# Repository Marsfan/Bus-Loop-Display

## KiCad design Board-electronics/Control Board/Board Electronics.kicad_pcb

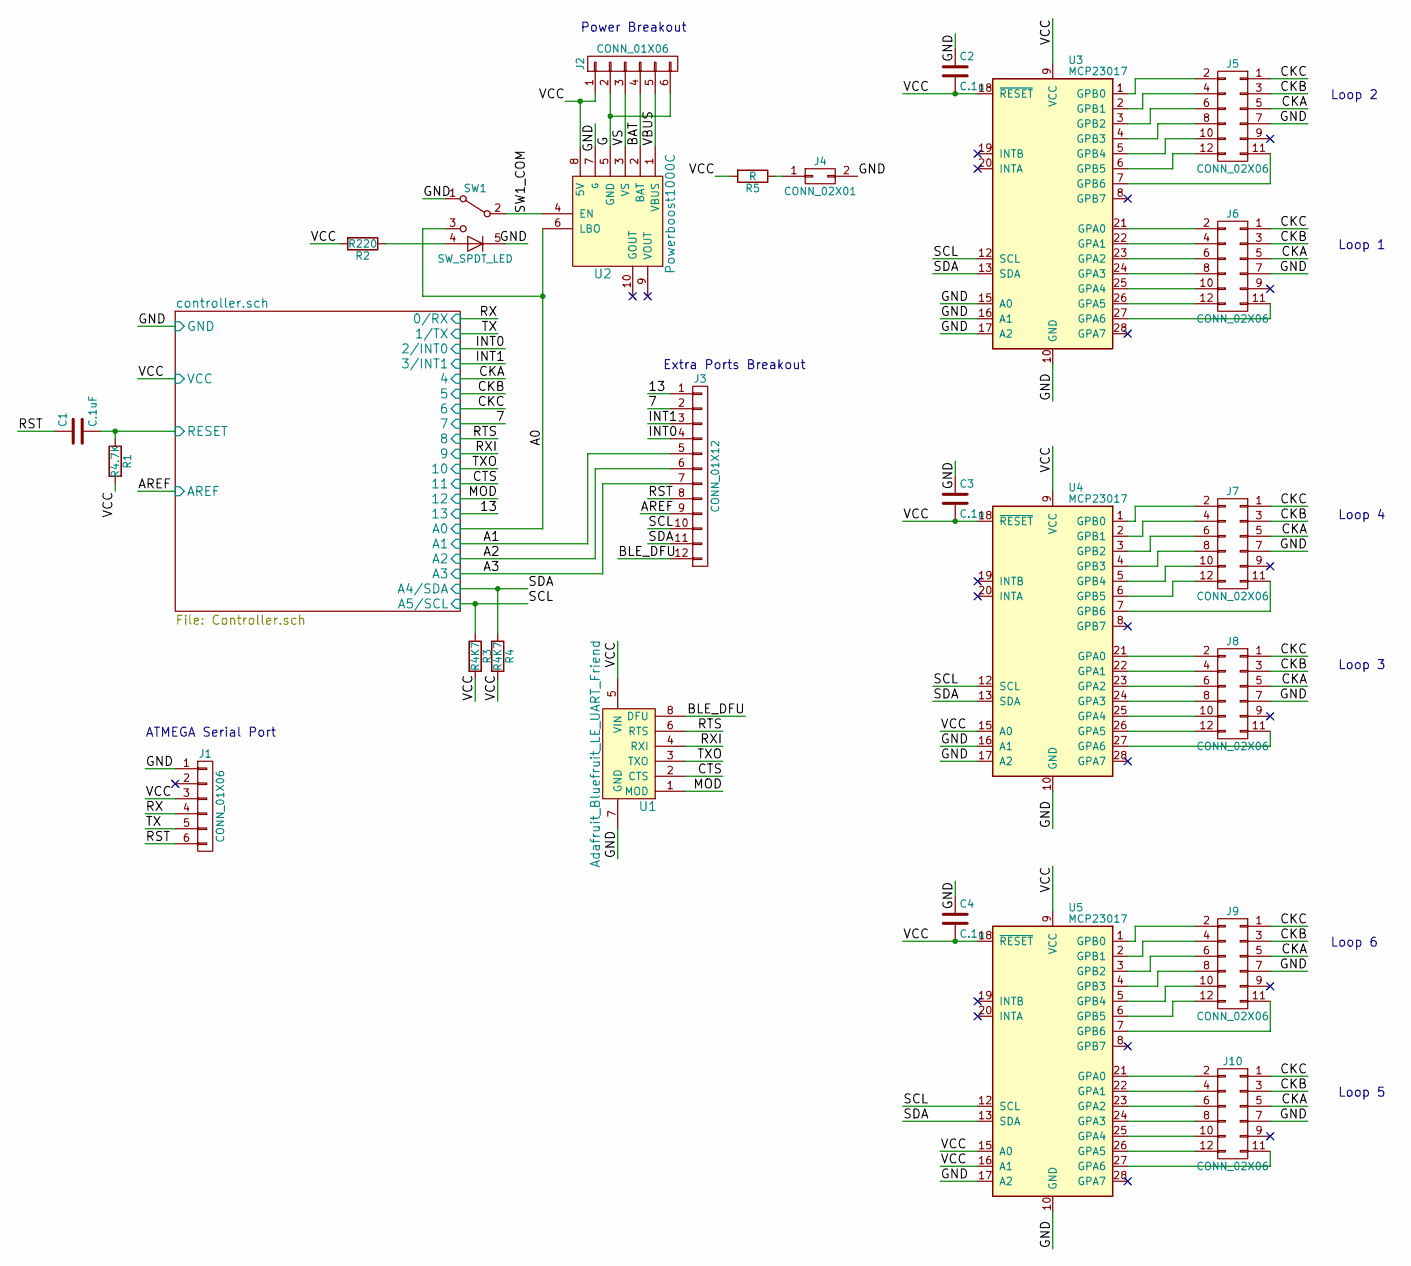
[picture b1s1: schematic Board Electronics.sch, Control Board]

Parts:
C1: C.1uF; C_Disc_D6.0mm_W4.4mm_P5.00mm
C2, C3, C4: C.1u; C_Disc_D6.0mm_W4.4mm_P5.00mm
J1, J2: CONN_01X06; Pin_Header_Straight_1x06_Pitch2.54mm
J3: CONN_01X12; Pin_Header_Straight_1x12_Pitch2.54mm
J4: CONN_02X01; Pin_Header_Straight_2x01_Pitch2.54mm
J5, J6, J7, J8, J9, J10: CONN_02X06; Picofit-12
R1: R4.7K; R_Axial_DIN0207_L6.3mm_D2.5mm_P10.16mm_Horizontal
R2: R220; R_Axial_DIN0207_L6.3mm_D2.5mm_P10.16mm_Horizontal
R3, R4: R4K7; R_Axial_DIN0207_L6.3mm_D2.5mm_P10.16mm_Horizontal
R5: R; R_Axial_DIN0207_L6.3mm_D2.5mm_P10.16mm_Horizontal
SW1: SW_SPDT_LED; Pin_Header_Straight_1x05_Pitch2.54mm
U1: Adafruit_Bluefruit_LE_UART_Friend; Blueferuit_LE_UART
U2: Powerboost1000C; Powerboost1000c
U3, U4, U5: MCP23017; DIP-28_W7.62mm_LongPads

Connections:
/7: J3.2; also elsewhere on the board
/13: J3.1; also elsewhere on the board
/A0: SW1.3 (C), U2.6 (LBO); also elsewhere on the board
/A1: J3.5; also elsewhere on the board
/A2: J3.6; also elsewhere on the board
/A3: J3.7; also elsewhere on the board
/AREF: J3.9; also elsewhere on the board
/BAT: J2.4, U2.2 (BAT)
/BLE_DFU: J3.12, U1.8 (DFU)
/CKA: J5.5, J6.5, J7.5, J8.5, J9.5, J10.5; also elsewhere on the board
/CKB: J5.3, J6.3, J7.3, J8.3, J9.3, J10.3; also elsewhere on the board
/CKC: J5.1, J6.1, J7.1, J8.1, J9.1, J10.1; also elsewhere on the board
/CTS: U1.2 (CTS); also elsewhere on the board
/G: J2.2, J2.6, U2.5 (GND)
/GND: C2.1, C3.1, C4.1, J1.1, J4.2, J5.7, J6.7, J7.7, J8.7, J9.7, J10.7, SW1.1 (A), SW1.5, U1.7 (GND), U2.7 (G), U3.10 (GND), U3.15 (A0), U3.16 (A1), U3.17 (A2), U4.10 (GND), U4.16 (A1), U4.17 (A2), U5.10 (GND), U5.17 (A2); also elsewhere on the board
/INT0: J3.4; also elsewhere on the board
/INT1: J3.3; also elsewhere on the board
/MOD: U1.1 (MOD); also elsewhere on the board
/RST: C1.1, J1.6, J3.8
/RTS: U1.6 (RTS); also elsewhere on the board
/RX: J1.4; also elsewhere on the board
/RXI: U1.4 (RXI); also elsewhere on the board
/SCL: J3.10, R3.1, U3.12 (SCL), U4.12 (SCL), U5.12 (SCL); also elsewhere on the board
/SDA: J3.11, R4.1, U3.13 (SDA), U4.13 (SDA), U5.13 (SDA); also elsewhere on the board
/SW1_COM: SW1.2 (B), U2.4 (EN)
/TX: J1.5; also elsewhere on the board
/TXO: U1.3 (TXO); also elsewhere on the board
/VBUS: J2.5, U2.1 (VBUS)
/VCC: C2.2, C3.2, C4.2, J1.3, J2.1, R1.2, R2.2, R3.2, R4.2, R5.2, U1.5 (VIN), U2.8 (5V), U3.9 (VCC), U3.18 (~RESET), U4.9 (VCC), U4.15 (A0), U4.18 (~RESET), U5.9 (VCC), U5.15 (A0), U5.16 (A1), U5.18 (~RESET); also elsewhere on the board
/VS: J2.3, U2.3 (VS)
/controller.sch/RESET: C1.2, R1.1; also elsewhere on the board
unnamed: J4.1, R5.1
unnamed: J5.2, U3.1 (GPB0)
unnamed: J5.4, U3.2 (GPB1)
unnamed: J5.6, U3.3 (GPB2)
unnamed: J5.8, U3.4 (GPB3)
unnamed: J5.10, U3.5 (GPB4)
unnamed: J5.11, U3.7 (GPB6)
unnamed: J5.12, U3.6 (GPB5)
unnamed: J6.2, U3.21 (GPA0)
unnamed: J6.4, U3.22 (GPA1)
unnamed: J6.6, U3.23 (GPA2)
unnamed: J6.8, U3.24 (GPA3)
unnamed: J6.10, U3.25 (GPA4)
unnamed: J6.11, U3.27 (GPA6)
unnamed: J6.12, U3.26 (GPA5)
unnamed: J7.2, U4.1 (GPB0)
unnamed: J7.4, U4.2 (GPB1)
unnamed: J7.6, U4.3 (GPB2)
unnamed: J7.8, U4.4 (GPB3)
unnamed: J7.10, U4.5 (GPB4)
unnamed: J7.11, U4.7 (GPB6)
unnamed: J7.12, U4.6 (GPB5)
unnamed: J8.2, U4.21 (GPA0)
unnamed: J8.4, U4.22 (GPA1)
unnamed: J8.6, U4.23 (GPA2)
unnamed: J8.8, U4.24 (GPA3)
unnamed: J8.10, U4.25 (GPA4)
unnamed: J8.11, U4.27 (GPA6)
unnamed: J8.12, U4.26 (GPA5)
unnamed: J9.2, U5.1 (GPB0)
unnamed: J9.4, U5.2 (GPB1)
unnamed: J9.6, U5.3 (GPB2)
unnamed: J9.8, U5.4 (GPB3)
unnamed: J9.10, U5.5 (GPB4)
unnamed: J9.11, U5.7 (GPB6)
unnamed: J9.12, U5.6 (GPB5)
unnamed: J10.2, U5.21 (GPA0)
unnamed: J10.4, U5.22 (GPA1)
unnamed: J10.6, U5.23 (GPA2)
unnamed: J10.8, U5.24 (GPA3)
unnamed: J10.10, U5.25 (GPA4)
unnamed: J10.11, U5.27 (GPA6)
unnamed: J10.12, U5.26 (GPA5)
unnamed: R2.1, SW1.4

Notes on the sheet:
ATMEGA Serial Port
Extra Ports Breakout
Power Breakout
Loop 1
Loop 2
Loop 3
Loop 4
Loop 5
Loop 6

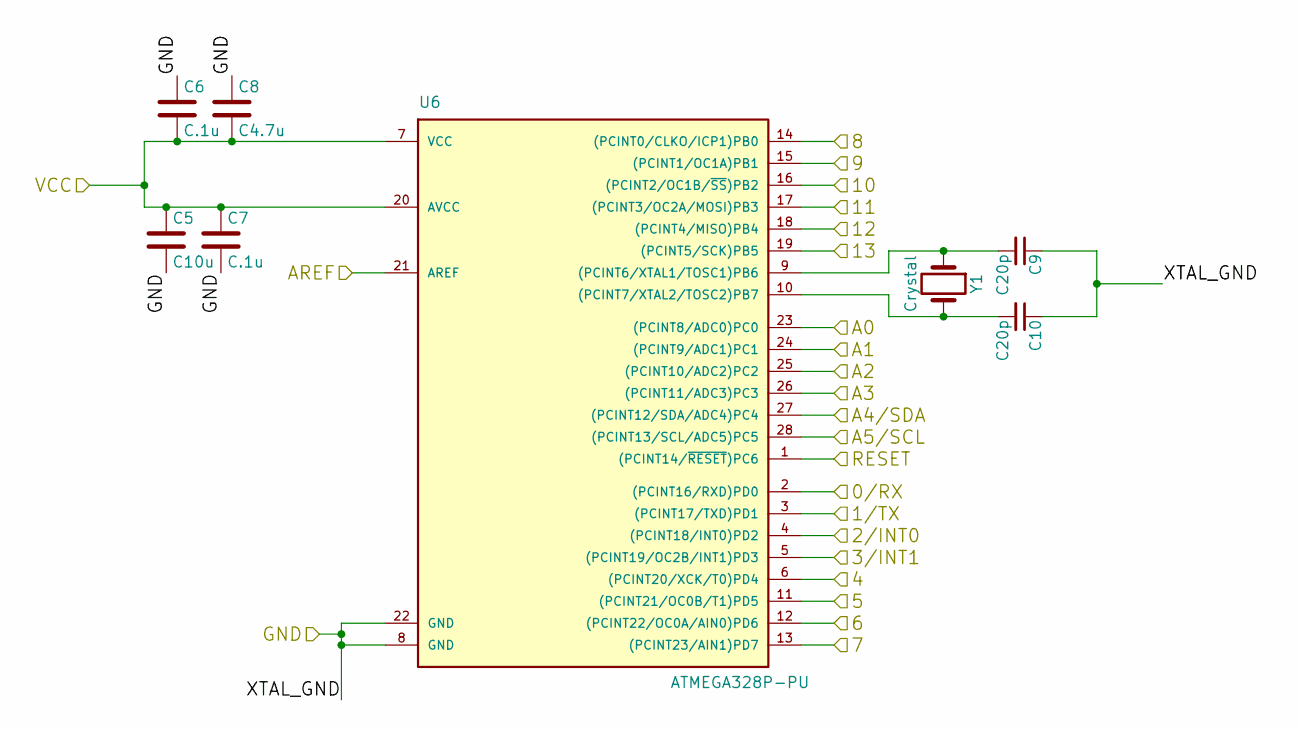
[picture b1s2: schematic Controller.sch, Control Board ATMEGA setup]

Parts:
C5: C10u; C_Disc_D6.0mm_W4.4mm_P5.00mm
C6, C7: C.1u; C_Disc_D6.0mm_W4.4mm_P5.00mm
C8: C4.7u; C_Disc_D7.5mm_W5.0mm_P5.00mm
C9, C10: C20p; C_Disc_D6.0mm_W2.5mm_P5.00mm
U6: ATMEGA328P-PU; DIP-28_W7.62mm_LongPads
Y1: Crystal; Crystal_HC49-U_Vertical

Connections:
/7: U6.13 ((PCINT23/AIN1)PD7); also elsewhere on the board
/13: U6.19 ((PCINT5/SCK)PB5); also elsewhere on the board
/A0: U6.23 ((PCINT8/ADC0)PC0); also elsewhere on the board
/A1: U6.24 ((PCINT9/ADC1)PC1); also elsewhere on the board
/A2: U6.25 ((PCINT10/ADC2)PC2); also elsewhere on the board
/A3: U6.26 ((PCINT11/ADC3)PC3); also elsewhere on the board
/AREF: U6.21 (AREF); also elsewhere on the board
/CKA: U6.6 ((PCINT20/XCK/T0)PD4); also elsewhere on the board
/CKB: U6.11 ((PCINT21/OC0B/T1)PD5); also elsewhere on the board
/CKC: U6.12 ((PCINT22/OC0A/AIN0)PD6); also elsewhere on the board
/CTS: U6.17 ((PCINT3/OC2A/MOSI)PB3); also elsewhere on the board
/GND: C5.2, C6.1, C7.2, C8.1, C9.1, C10.1, U6.8 (GND), U6.22 (GND); also elsewhere on the board
/INT0: U6.4 ((PCINT18/INT0)PD2); also elsewhere on the board
/INT1: U6.5 ((PCINT19/OC2B/INT1)PD3); also elsewhere on the board
/MOD: U6.18 ((PCINT4/MISO)PB4); also elsewhere on the board
/RTS: U6.14 ((PCINT0/CLKO/ICP1)PB0); also elsewhere on the board
/RX: U6.2 ((PCINT16/RXD)PD0); also elsewhere on the board
/RXI: U6.15 ((PCINT1/OC1A)PB1); also elsewhere on the board
/SCL: U6.28 ((PCINT13/SCL/ADC5)PC5); also elsewhere on the board
/SDA: U6.27 ((PCINT12/SDA/ADC4)PC4); also elsewhere on the board
/TX: U6.3 ((PCINT17/TXD)PD1); also elsewhere on the board
/TXO: U6.16 ((PCINT2/OC1B/~SS~)PB2); also elsewhere on the board
/VCC: C5.1, C6.2, C7.1, C8.2, U6.7 (VCC), U6.20 (AVCC); also elsewhere on the board
/controller.sch/RESET: U6.1 ((PCINT14/~RESET~)PC6); also elsewhere on the board
unnamed: C9.2, U6.9 ((PCINT6/XTAL1/TOSC1)PB6), Y1.1
unnamed: C10.2, U6.10 ((PCINT7/XTAL2/TOSC2)PB7), Y1.2

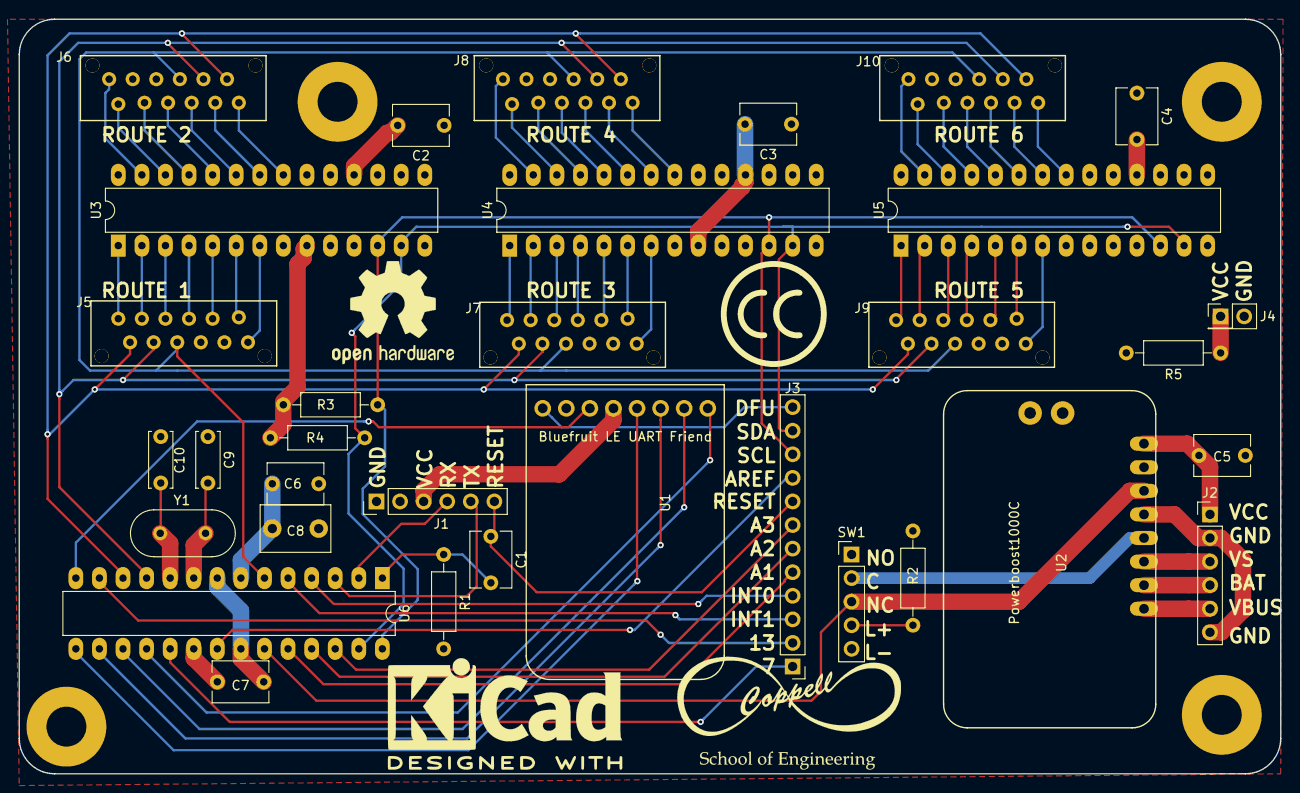
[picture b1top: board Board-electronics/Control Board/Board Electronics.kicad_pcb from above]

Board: 2 copper layers, 135.9 x 81.3 mm, 37 parts (0 on the bottom side), 77 nets.

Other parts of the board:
M4, M4#2, M4#3, M4#4: MountingHole_4.3mm_M4_Pad

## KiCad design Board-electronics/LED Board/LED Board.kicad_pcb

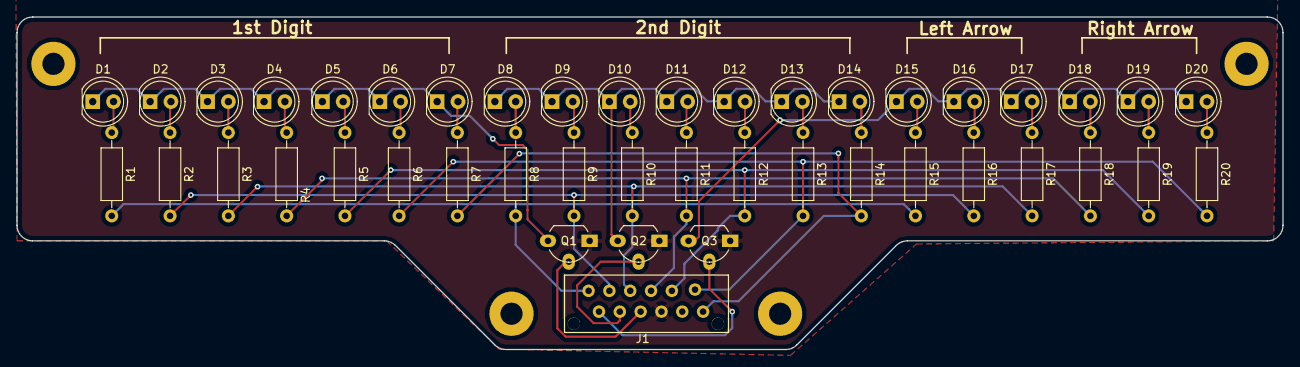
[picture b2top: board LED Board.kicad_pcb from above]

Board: 2 copper layers, 154.4 x 40.6 mm, 44 parts (0 on the bottom side), 34 nets.

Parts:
D1, D2, D3, D4, D5, D6, D7, D8, D9, D10, D11, D12, D13, D14, D15, D16, D17, D18, D19, D20: LED; LED_D5.0mm
J1: CONN_02X06; Picofit-12
Q1, Q2, Q3: PN2222A; TO-92_Molded_Wide_Oval
R1, R2, R3, R4, R5, R6, R7, R8, R9, R10, R11, R12, R13, R14, R15, R16, R17, R18, R19, R20: R; R_Axial_DIN0207_L6.3mm_D2.5mm_P10.16mm_Horizontal

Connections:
/A: J1.2, R1.2, R8.2, R15.2
/B: J1.4, R2.2, R9.2, R16.2
/C: J1.6, R3.2, R10.2, R17.2
/CKA: J1.5, Q1.2
/CKB: J1.3, Q2.2
/CKC: J1.1, Q3.2
/D: J1.8, R4.2, R11.2, R18.2
/E: J1.10, R5.2, R12.2, R19.2
/F: J1.12, R6.2, R13.2, R20.2
/G: J1.11, R7.2, R14.2
/GND: J1.7, Q1.1, Q2.1, Q3.1
unnamed: D1.1, D2.1, D3.1, D4.1, D5.1, D6.1, D7.1, Q1.3
unnamed: D1.2, R1.1
unnamed: D2.2, R2.1
unnamed: D3.2, R3.1
unnamed: D4.2, R4.1
unnamed: D5.2, R5.1
unnamed: D6.2, R6.1
unnamed: D7.2, R7.1
unnamed: D8.2, R8.1
unnamed: D9.2, R9.1
unnamed: D8.1, D9.1, D10.1, D11.1, D12.1, D13.1, D14.1, Q2.3
unnamed: D10.2, R10.1
unnamed: D11.2, R11.1
unnamed: D12.2, R12.1
unnamed: D13.2, R13.1
unnamed: D14.2, R14.1
unnamed: D15.1, D16.1, D17.1, D18.1, D19.1, D20.1, Q3.3
unnamed: D15.2, R15.1
unnamed: D16.2, R16.1
unnamed: D17.2, R17.1
unnamed: D18.2, R18.1
unnamed: D19.2, R19.1
unnamed: D20.2, R20.1

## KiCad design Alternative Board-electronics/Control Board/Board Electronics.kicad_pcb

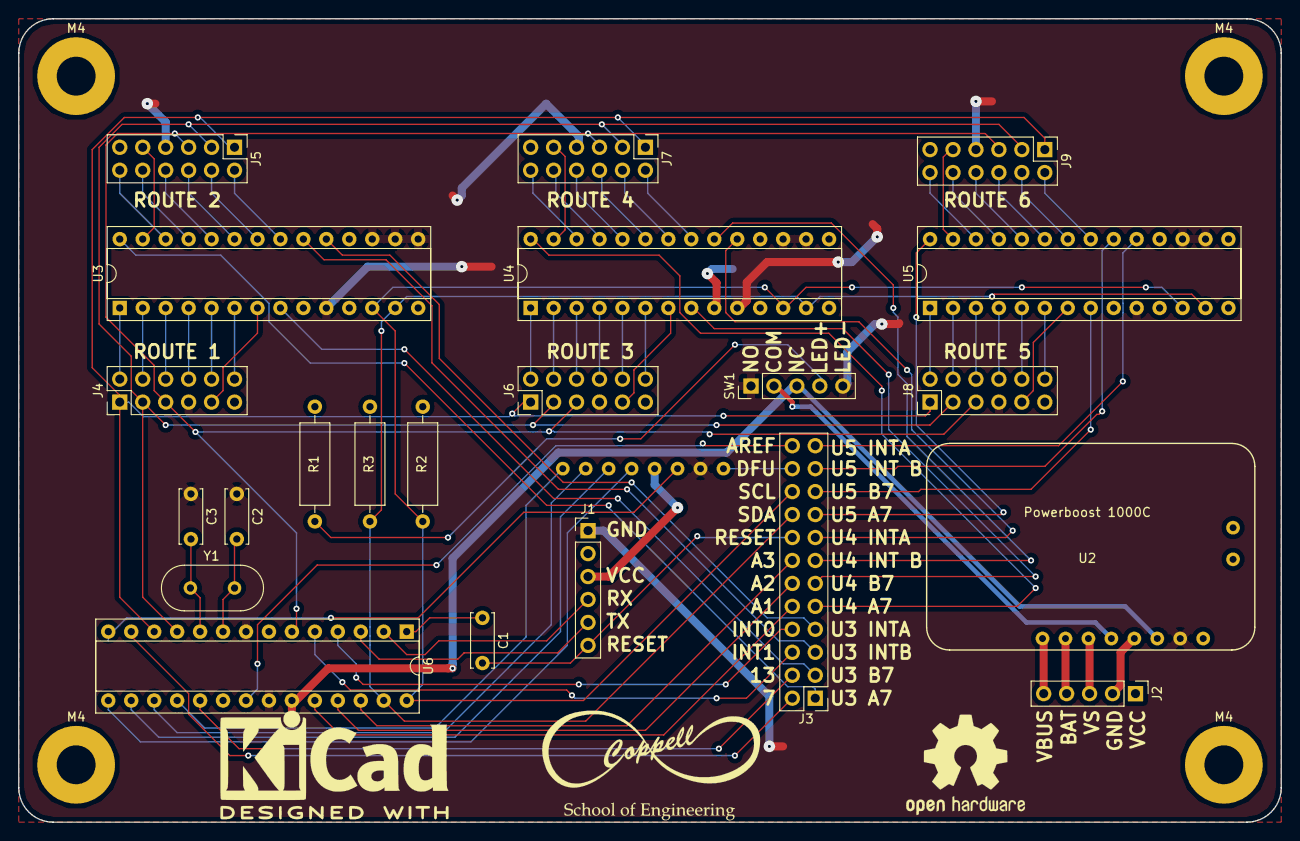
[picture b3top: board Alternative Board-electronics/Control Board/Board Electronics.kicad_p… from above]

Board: 2 copper layers, 139.7 x 88.9 mm, 27 parts (1 on the bottom side), 88 nets.

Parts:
C1: C.1uF; C_Disc_D6.0mm_W2.5mm_P5.00mm
C2, C3: C20p; C_Disc_D6.0mm_W2.5mm_P5.00mm
J1: CONN_01X06; Pin_Header_Straight_1x06_Pitch2.54mm
J2: CONN_01X05; Pin_Header_Straight_1x05_Pitch2.54mm
J3: CONN_02X12; Pin_Header_Straight_2x12_Pitch2.54mm
J4, J5, J6, J7, J8, J9: CONN_02X06; Pin_Header_Straight_2x06_Pitch2.54mm
M4, M4#2, M4#3, M4#4: MountingHole_4.3mm_M4_Pad
R1: R220; R_Axial_DIN0309_L9.0mm_D3.2mm_P12.70mm_Horizontal
R2, R3: R4K7; R_Axial_DIN0309_L9.0mm_D3.2mm_P12.70mm_Horizontal
SW1: SW_SPDT_LED; Pin_Header_Straight_1x05_Pitch2.54mm
U1: Adafruit_Bluefruit_LE_UART_Friend; Blueferuit_LE_UART
U2: Powerboost 1000C; Powerboost1000c
U3, U4, U5: MCP23017; DIP-28_W7.62mm_Socket
U6: ATMEGA328P-PU; DIP-28_W7.62mm_Socket
Y1: Crystal; Crystal_HC49-U_Vertical

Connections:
/7: J3.2, U6.13
/13: J3.4, U6.19
/AREF: J3.24, U6.21
/BLE_DFU: J3.22, U1.8
/CKA: J4.5, J5.5, J6.5, J7.5, J8.5, J9.5, U6.6
/CKB: J4.3, J5.3, J6.3, J7.3, J8.3, J9.3, U6.11
/CKC: J4.1, J5.1, J6.1, J7.1, J8.1, J9.1, U6.12
/CTS: U1.2, U6.17
/GND: C2.1, C3.1, J1.1, J4.7, J5.7, J6.7, J7.7, J8.7, J9.7, SW1.1, SW1.5, U1.7, U2.7, U3.10, U3.15, U3.16, U3.17, U4.10, U4.16, U4.17, U5.10, U5.16, U5.17, U6.8, U6.22
/INT0: J3.8, U6.4
/INT1: J3.6, U6.5
/MOD: U1.1, U6.18
/RST: C1.2, J1.6, J3.16
/RTS: U1.6, U6.14
/RX: J1.4, U6.2
/RXI: U1.4, U6.15
/SCL: J3.20, R2.1, U3.12, U4.12, U5.12, U6.28
/SDA: J3.18, R3.1, U3.13, U4.13, U5.13, U6.27
/TX: J1.5, U6.3
/TXO: U1.3, U6.16
/U3A7: J3.1, U3.28
/U3B7: J3.3, U3.8
/U3INTA: J3.5, U3.20
/U3INTB: J3.7, U3.19
/U4A7: J3.9, U4.28
/U4B7: J3.11, U4.8
/U4INTA: J3.13, U4.20
/U4INTB: J3.15, U4.19
/U5A7: J3.17, U5.28
/U5B7: J3.19, U5.8
/U5INTA: J3.21, U5.20
/U5INTB: J3.23, U5.19
/VCC: J1.3, J2.1, R1.2, R2.2, R3.2, U1.5, U2.8, U3.9, U3.18, U4.9, U4.15, U4.18, U5.9, U5.15, U5.18, U6.7, U6.20
/controller.sch/A0: SW1.3, U2.6, U6.23
/controller.sch/A1: J3.10, U6.24
/controller.sch/A2: J3.12, U6.25
/controller.sch/A3: J3.14, U6.26
/controller.sch/RESET: C1.1, U6.1
unnamed: C2.2, U6.9, Y1.1
unnamed: C3.2, U6.10, Y1.2
unnamed: J2.2, U2.5
unnamed: J2.3, U2.3
unnamed: J2.4, U2.2
unnamed: J2.5, U2.1
unnamed: J4.2, U3.1
unnamed: J4.4, U3.2
unnamed: J4.6, U3.3
unnamed: J4.8, U3.4
unnamed: J4.9, U3.7
unnamed: J4.10, U3.5
unnamed: J4.12, U3.6
unnamed: J5.2, U3.21
unnamed: J5.4, U3.22
unnamed: J5.6, U3.23
unnamed: J5.8, U3.24
unnamed: J5.9, U3.27
unnamed: J5.10, U3.25
unnamed: J5.12, U3.26
unnamed: J6.2, U4.1
unnamed: J6.4, U4.2
unnamed: J6.6, U4.3
unnamed: J6.8, U4.4
unnamed: J6.9, U4.7
unnamed: J6.10, U4.5
unnamed: J6.12, U4.6
unnamed: J7.2, U4.21
unnamed: J7.4, U4.22
unnamed: J7.6, U4.23
unnamed: J7.8, U4.24
unnamed: J7.9, U4.27
unnamed: J7.10, U4.25
unnamed: J7.12, U4.26
unnamed: J8.2, U5.1
unnamed: J8.4, U5.2
unnamed: J8.6, U5.3
unnamed: J8.8, U5.4
unnamed: J8.9, U5.7
unnamed: J8.10, U5.5
unnamed: J8.12, U5.6
unnamed: J9.2, U5.21
unnamed: J9.4, U5.22
unnamed: J9.6, U5.23
unnamed: J9.8, U5.24
unnamed: J9.9, U5.27
unnamed: J9.10, U5.25
unnamed: J9.12, U5.26
unnamed: R1.1, SW1.4
unnamed: SW1.2, U2.4

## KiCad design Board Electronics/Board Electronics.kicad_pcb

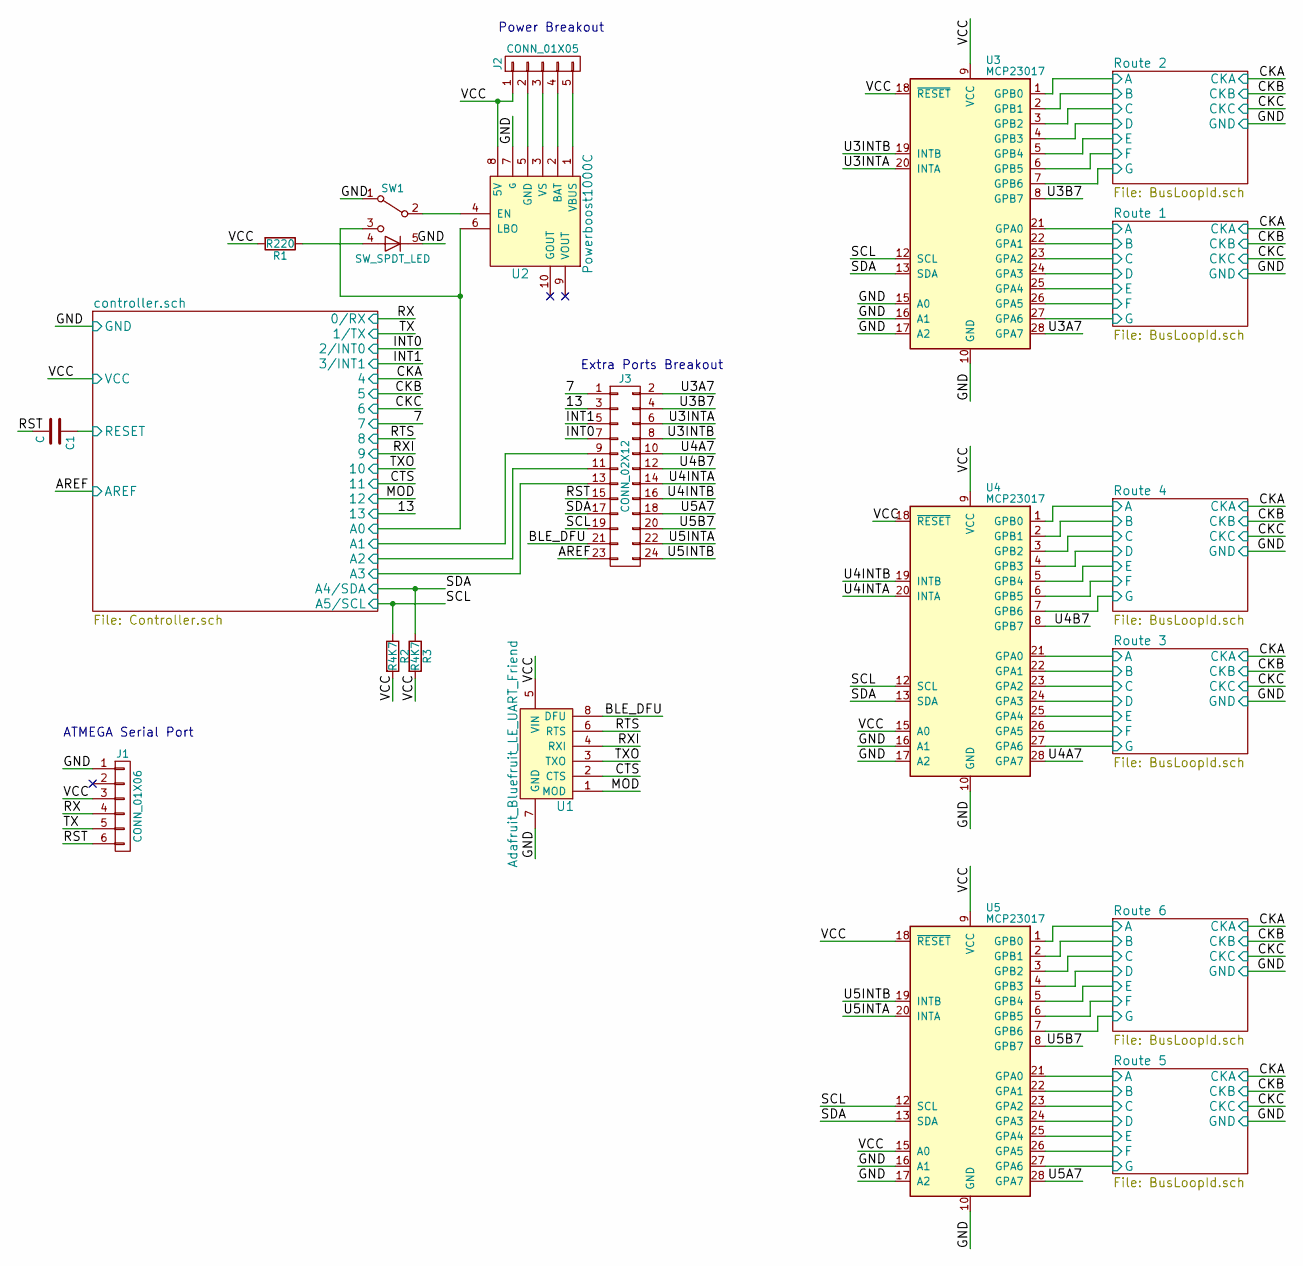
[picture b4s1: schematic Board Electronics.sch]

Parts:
C1: C; C_Disc_D6.0mm_W2.5mm_P5.00mm
J1: CONN_01X06; Pin_Header_Straight_1x06_Pitch2.54mm
J2: CONN_01X05; Pin_Header_Straight_1x05_Pitch2.54mm
J3: CONN_02X12; Pin_Header_Straight_2x12_Pitch2.54mm
R1: R220; R_Axial_DIN0309_L9.0mm_D3.2mm_P12.70mm_Horizontal
R2, R3: R4K7; R_Axial_DIN0309_L9.0mm_D3.2mm_P12.70mm_Horizontal
SW1: SW_SPDT_LED; Pin_Header_Straight_1x05_Pitch2.54mm
U1: Adafruit_Bluefruit_LE_UART_Friend; Blueferuit_LE_UART
U2: Powerboost1000C; Powerboost1000c
U3, U4, U5: MCP23017; DIP-28_W7.62mm_Socket

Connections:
/7: J3.1; also elsewhere on the board
/13: J3.3; also elsewhere on the board
/AREF: J3.23; also elsewhere on the board
/BLE_DFU: J3.21, U1.8 (DFU)
/CTS: U1.2 (CTS); also elsewhere on the board
/GND: J1.1, SW1.1 (A), SW1.5, U1.7 (GND), U2.7 (G), U3.10 (GND), U3.15 (A0), U3.16 (A1), U3.17 (A2), U4.10 (GND), U4.16 (A1), U4.17 (A2), U5.10 (GND), U5.16 (A1), U5.17 (A2); also elsewhere on the board
/INT0: J3.7; also elsewhere on the board
/INT1: J3.5; also elsewhere on the board
/MOD: U1.1 (MOD); also elsewhere on the board
/RST: C1.2, J1.6, J3.15
/RTS: U1.6 (RTS); also elsewhere on the board
/RX: J1.4; also elsewhere on the board
/RXI: U1.4 (RXI); also elsewhere on the board
/Route 1/A: U3.21 (GPA0); also elsewhere on the board
/Route 1/B: U3.22 (GPA1); also elsewhere on the board
/Route 1/C: U3.23 (GPA2); also elsewhere on the board
/Route 1/D: U3.24 (GPA3); also elsewhere on the board
/Route 1/E: U3.25 (GPA4); also elsewhere on the board
/Route 1/F: U3.26 (GPA5); also elsewhere on the board
/Route 1/G: U3.27 (GPA6); also elsewhere on the board
/Route 2/A: U3.1 (GPB0); also elsewhere on the board
/Route 2/B: U3.2 (GPB1); also elsewhere on the board
/Route 2/C: U3.3 (GPB2); also elsewhere on the board
/Route 2/D: U3.4 (GPB3); also elsewhere on the board
/Route 2/E: U3.5 (GPB4); also elsewhere on the board
/Route 2/F: U3.6 (GPB5); also elsewhere on the board
/Route 2/G: U3.7 (GPB6); also elsewhere on the board
/Route 3/A: U4.21 (GPA0); also elsewhere on the board
/Route 3/B: U4.22 (GPA1); also elsewhere on the board
/Route 3/C: U4.23 (GPA2); also elsewhere on the board
/Route 3/D: U4.24 (GPA3); also elsewhere on the board
/Route 3/E: U4.25 (GPA4); also elsewhere on the board
/Route 3/F: U4.26 (GPA5); also elsewhere on the board
/Route 3/G: U4.27 (GPA6); also elsewhere on the board
/Route 4/A: U4.1 (GPB0); also elsewhere on the board
/Route 4/B: U4.2 (GPB1); also elsewhere on the board
/Route 4/C: U4.3 (GPB2); also elsewhere on the board
/Route 4/D: U4.4 (GPB3); also elsewhere on the board
/Route 4/E: U4.5 (GPB4); also elsewhere on the board
/Route 4/F: U4.6 (GPB5); also elsewhere on the board
/Route 4/G: U4.7 (GPB6); also elsewhere on the board
/Route 5/A: U5.21 (GPA0); also elsewhere on the board
/Route 5/B: U5.22 (GPA1); also elsewhere on the board
/Route 5/C: U5.23 (GPA2); also elsewhere on the board
/Route 5/D: U5.24 (GPA3); also elsewhere on the board
/Route 5/E: U5.25 (GPA4); also elsewhere on the board
/Route 5/F: U5.26 (GPA5); also elsewhere on the board
/Route 5/G: U5.27 (GPA6); also elsewhere on the board
/Route 6/A: U5.1 (GPB0); also elsewhere on the board
/Route 6/B: U5.2 (GPB1); also elsewhere on the board
/Route 6/C: U5.3 (GPB2); also elsewhere on the board
/Route 6/D: U5.4 (GPB3); also elsewhere on the board
/Route 6/E: U5.5 (GPB4); also elsewhere on the board
/Route 6/F: U5.6 (GPB5); also elsewhere on the board
/Route 6/G: U5.7 (GPB6); also elsewhere on the board
/SCL: J3.19, R2.1, U3.12 (SCL), U4.12 (SCL), U5.12 (SCL); also elsewhere on the board
/SDA: J3.17, R3.1, U3.13 (SDA), U4.13 (SDA), U5.13 (SDA); also elsewhere on the board
/TX: J1.5; also elsewhere on the board
/TXO: U1.3 (TXO); also elsewhere on the board
/U3A7: J3.2, U3.28 (GPA7)
/U3B7: J3.4, U3.8 (GPB7)
/U3INTA: J3.6, U3.20 (INTA)
/U3INTB: J3.8, U3.19 (INTB)
/U4A7: J3.10, U4.28 (GPA7)
/U4B7: J3.12, U4.8 (GPB7)
/U4INTA: J3.14, U4.20 (INTA)
/U4INTB: J3.16, U4.19 (INTB)
/U5A7: J3.18, U5.28 (GPA7)
/U5B7: J3.20, U5.8 (GPB7)
/U5INTA: J3.22, U5.20 (INTA)
/U5INTB: J3.24, U5.19 (INTB)
/VCC: J1.3, J2.1, R1.2, R2.2, R3.2, U1.5 (VIN), U2.8 (5V), U3.9 (VCC), U3.18 (~RESET), U4.9 (VCC), U4.15 (A0), U4.18 (~RESET), U5.9 (VCC), U5.15 (A0), U5.18 (~RESET); also elsewhere on the board
/controller.sch/A0: SW1.3 (C), U2.6 (LBO); also elsewhere on the board
/controller.sch/A1: J3.9; also elsewhere on the board
/controller.sch/A2: J3.11; also elsewhere on the board
/controller.sch/A3: J3.13; also elsewhere on the board
/controller.sch/RESET: C1.1; also elsewhere on the board
unnamed: J2.2, U2.5 (GND)
unnamed: J2.3, U2.3 (VS)
unnamed: J2.4, U2.2 (BAT)
unnamed: J2.5, U2.1 (VBUS)
unnamed: R1.1, SW1.4
unnamed: SW1.2 (B), U2.4 (EN)

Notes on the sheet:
ATMEGA Serial Port
Extra Ports Breakout
Power Breakout
